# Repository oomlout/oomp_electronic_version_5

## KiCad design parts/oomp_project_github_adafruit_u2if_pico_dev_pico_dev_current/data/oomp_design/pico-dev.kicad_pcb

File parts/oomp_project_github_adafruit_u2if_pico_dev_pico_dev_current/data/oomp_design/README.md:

# OOMP KiCad design copy

Open `pico-dev.kicad_pro` (or the `.kicad_pcb` / `.kicad_sch`) in KiCad. Local OOMP libraries are under `libraries/`. Original inputs are preserved in [../original/](../original/).

Only verified unchanged installed KiCad defaults were renamed. Modified, custom, unmatched and unavailable items remain unchanged. Soldering variants are never swapped during conversion. Existing pad coordinates, nets and UUIDs are preserved.

See [conversion_report.yaml](conversion_report.yaml) for every conversion and skip. Copy this directory before editing; regeneration refuses to overwrite edited design files.

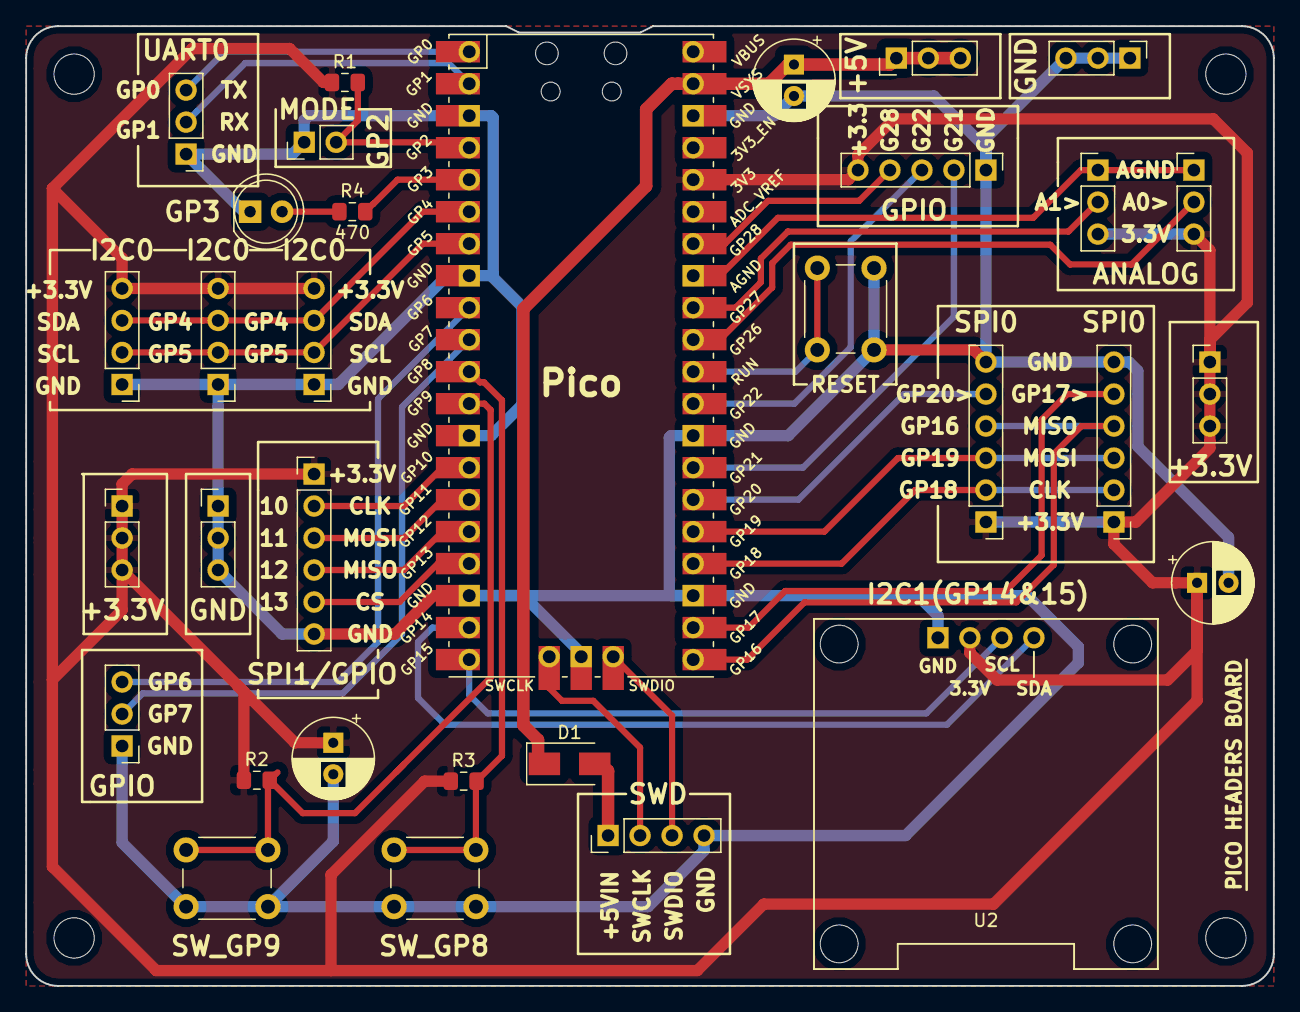
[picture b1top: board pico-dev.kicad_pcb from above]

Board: 2 copper layers, 99.1 x 76.2 mm, 36 parts (0 on the bottom side), 35 nets.

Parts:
C1, C2, C3: CP; CP_Radial_D6.3mm_P2.50mm
D1: SS14; D_SMA
D2: LED; LED_D5.0mm
H1, H2, H3, H4: MountingHole; MountingHole_3.2mm_M3
J1: MODE; PinHeader_1x02_P2.54mm_Vertical
J2: SWD; PinHeader_1x04_P2.54mm_Vertical
J3: AN0_GP26; PinHeader_1x03_P2.54mm_Vertical
J4: AN1_GP27; PinHeader_1x03_P2.54mm_Vertical
J5, J6, J7: I2C0; PinHeader_1x04_P2.54mm_Vertical
J8: UART0; PinHeader_1x03_P2.54mm_Vertical
J9, J10: SPI0; PinHeader_1x06_P2.54mm_Vertical
J11: GPIO; PinHeader_1x05_P2.54mm_Vertical
J12: SPI1/GPIO; PinHeader_1x06_P2.54mm_Vertical
J13, J17: +3.3V; PinHeader_1x03_P2.54mm_Vertical
J14: +5V; PinHeader_1x03_P2.54mm_Vertical
J15, J16: GND; PinHeader_1x03_P2.54mm_Vertical
J18: GPIO; PinHeader_1x03_P2.54mm_Vertical
R1, R2, R3: 10k; R_0805_2012Metric_Pad1.15x1.40mm_HandSolder
R4: 470; R_0805_2012Metric_Pad1.15x1.40mm_HandSolder
SW1: SW_RST; SW_PUSH_6mm_H4.3mm
SW2: SW_GP9; SW_PUSH_6mm_H4.3mm
SW3: SW_GP8; SW_PUSH_6mm_H4.3mm
U1: Pico; RPi_Pico_SMD_TH
U2: SSD1306_I2C; ssd1306_I2c

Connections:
+3V3: C2.1, C3.1, J3.3, J4.3, J5.4, J6.4, J7.4, J9.1, J10.1, J11.5, J12.1, J13.1, J13.2, J13.3, J17.1, J17.2, J17.3, R1.1, R2.1, R3.1, U1.36, U2.2
+5V: C1.1, D1.1, J14.1, J14.2, J14.3, U1.39
+5VD: D1.2, J2.1
ADC0: J3.2, U1.31
ADC1: J4.2, U1.32
AGND: J3.1, J4.1, U1.33
GND: C1.2, C2.2, C3.2, D2.1, J1.1, J2.4, J5.1, J6.1, J7.1, J8.1, J9.6, J10.6, J11.1, J12.6, J15.1, J15.2, J15.3, J16.1, J16.2, J16.3, J18.1, SW1.2, SW2.2, SW3.2, U1.3, U1.8, U1.13, U1.18, U1.23, U1.28, U1.38, U1.42, U2.1
GP6: J18.3, U1.9
GP7: J18.2, U1.10
GP8: R3.2, SW3.1, U1.11
GP9: R2.2, SW2.1, U1.12
GP21: J11.2, U1.27
GP22: J11.3, U1.29
GP28: J11.4, U1.34
LED0: R4.2, U1.5
MODE: J1.2, R1.2, U1.4
unnamed: D2.2, R4.1
RUN: SW1.1, U1.30
SCL_0: J5.2, J6.2, J7.2, U1.7
SCL_1: U1.20, U2.3
SDA_0: J5.3, J6.3, J7.3, U1.6
SDA_1: U1.19, U2.4
SPI0_CK: J9.2, J10.2, U1.24
SPI0_CS1: J9.5, U1.22
SPI0_CS2: J10.5, U1.26
SPI0_MISO: J9.4, J10.4, U1.21
SPI0_MOSI: J9.3, J10.3, U1.25
SPI1_CK_GP10: J12.2, U1.14
SPI1_CS1_GP13: J12.5, U1.17
SPI1_MISO_GP12: J12.4, U1.16
SPI1_MOSI_GP11: J12.3, U1.15
SWCLK: J2.2, U1.41
SWDIO: J2.3, U1.43
U_RX: J8.2, U1.2
U_TX: J8.3, U1.1

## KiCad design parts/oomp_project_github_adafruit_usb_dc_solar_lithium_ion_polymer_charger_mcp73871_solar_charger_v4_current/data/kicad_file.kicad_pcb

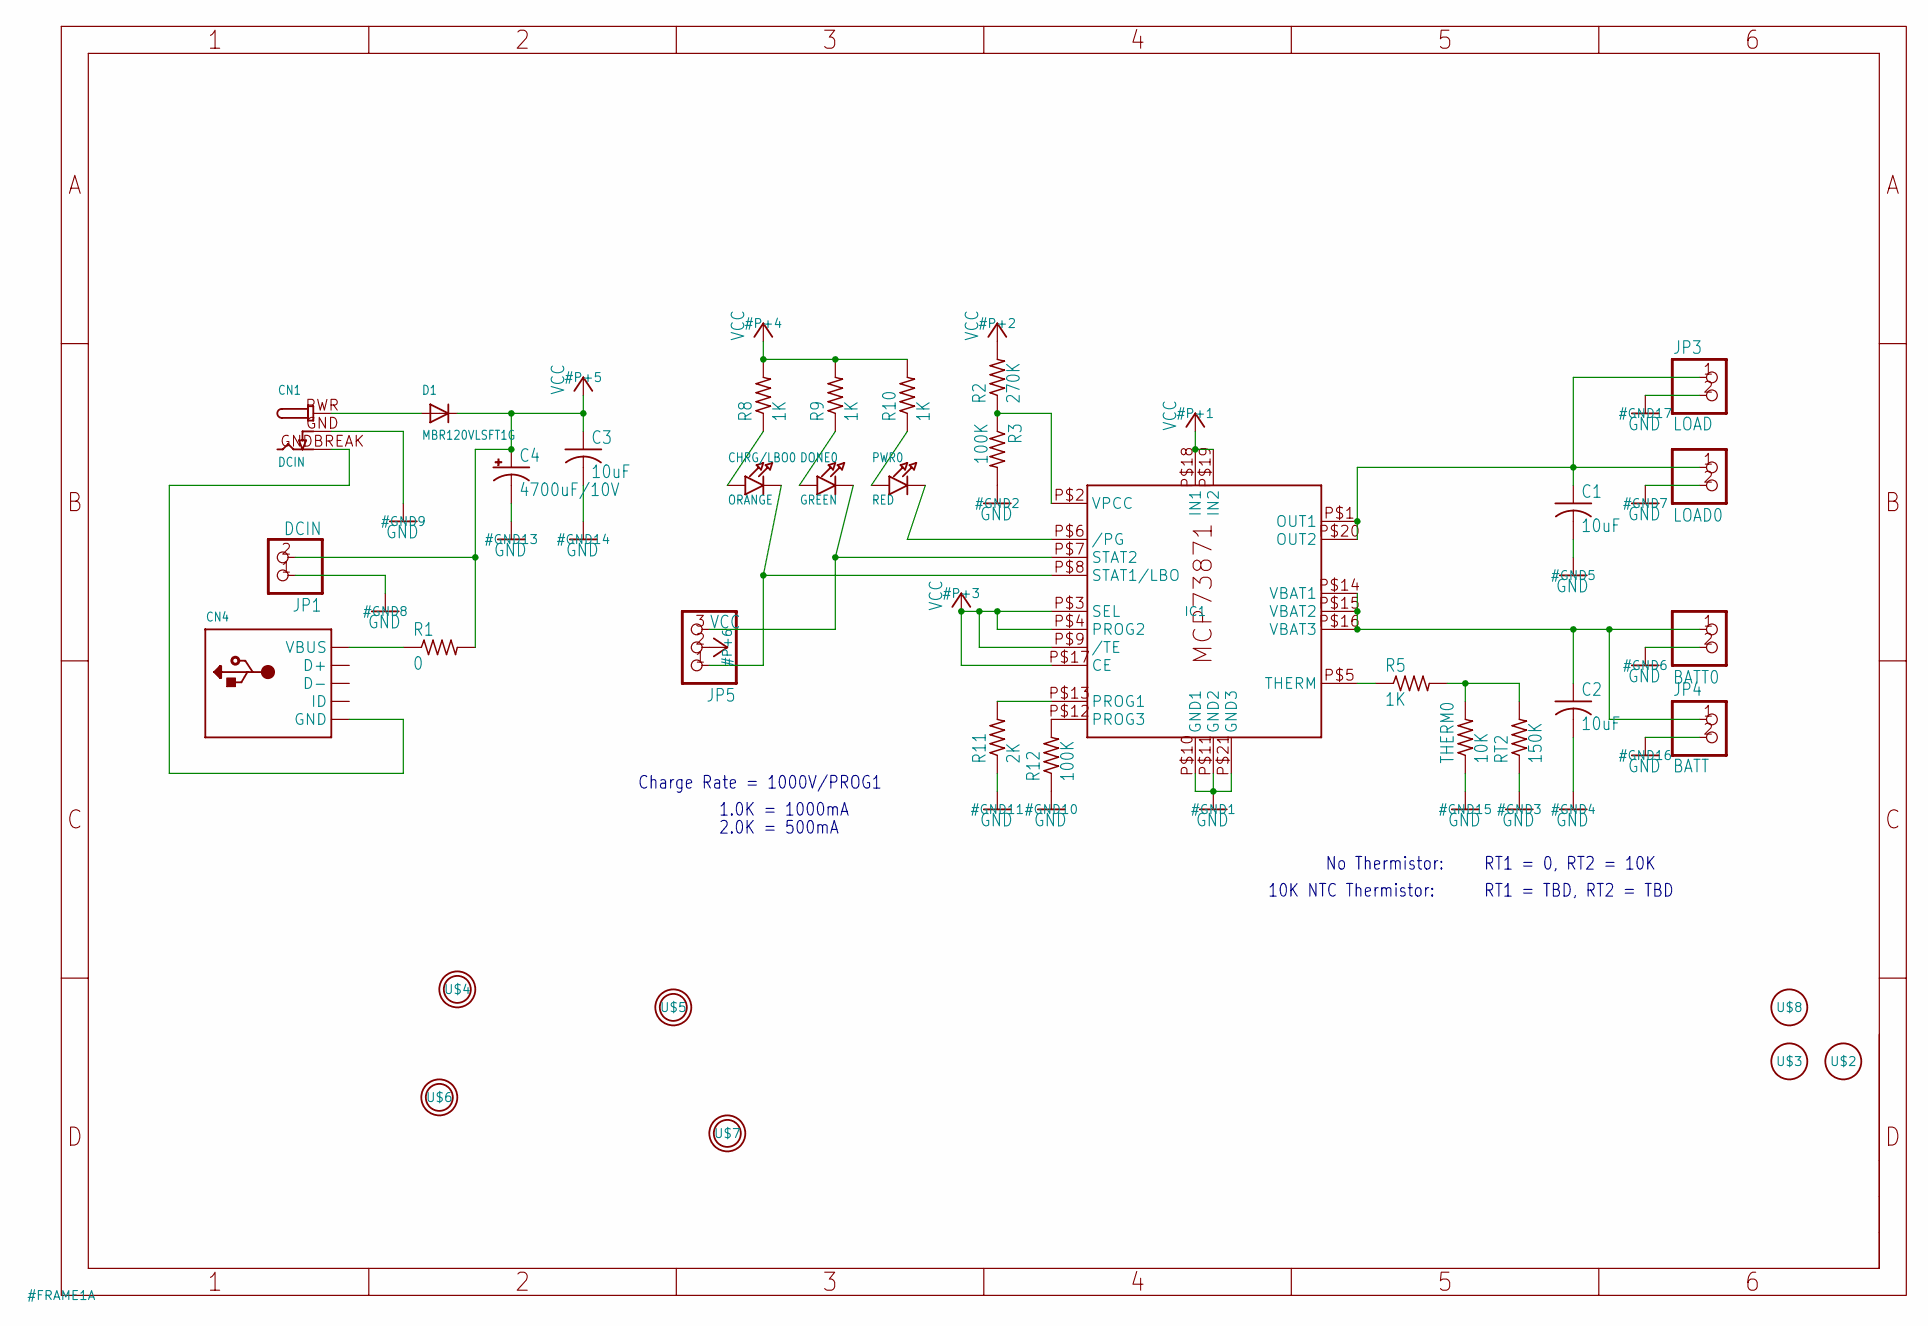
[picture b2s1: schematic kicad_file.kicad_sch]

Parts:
BATT0: JST_2PIN-SMT-RA; JST-PH-2-SMT-RA
C1, C2, C3: 10uF; C0805K
C4: 4700uF/10V; E5-13
CHRG/LBO0: ORANGE; CHIPLED_0805_NOOUTLINE
CN1: DCIN; DCJACK_2MM_SMT
CN4: USBMINIBLARGE; USB-MINIB_LARGER
D1: MBR120VLSFT1G; SOD-123
DONE0: GREEN; CHIPLED_0805_NOOUTLINE
IC1: MCP73871; QFN20_4MM
JP1: DCIN; 1X02_OVAL
JP3: LOAD; 1X02_ROUND
JP4: BATT; 1X02_ROUND
JP5: PINHD-1X3CB; 1X03-CLEANBIG
LOAD0: JST_2PIN-SMT-RA; JST-PH-2-SMT-RA
PWR0: RED; CHIPLED_0805_NOOUTLINE
R1: 0; R0805
R2: 270K; R0805
R3, R12: 100K; R0805
R5: 1K; M0805
R8, R9, R10: 1K; R0805
R11: 2K; 0805-THM
RT2: 150K; M0805
THERM0: 10K; 0805-THM
U$2, U$3, U$8: FIDUCIAL; FIDUCIAL_1MM
U$4, U$5, U$6, U$7: MOUNTINGHOLE2.5; MOUNTINGHOLE_2.5_PLATED

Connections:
BATT: BATT0.1 (2), C2.1, IC1.P$14 (VBAT1), IC1.P$15 (VBAT2), IC1.P$16 (VBAT3), JP4.1
GND: BATT0.2 (1), C1.2, C2.2, C3.2, C4.-, CN1.GND (GNDBREAK), IC1.P$10 (GND1), IC1.P$11 (GND2), IC1.P$21 (GND3), JP1.1, JP3.2, JP4.2, LOAD0.2 (1), R3.2, R11.1, R12.1, RT2.1, THERM0.1
unnamed: IC1.P$6 (/PG), PWR0.C
unnamed: CN4.VBUS, R1.1
unnamed: CN1.GNDBREAK (GND), CN4.GND, CN4.GND1 (GND), CN4.GND2 (GND), CN4.GND3 (GND), CN4.GND4 (GND)
unnamed: DONE0.C, IC1.P$7 (STAT2), JP5.3
unnamed: IC1.P$5 (THERM), R5.1
unnamed: IC1.P$2 (VPCC), R2.1, R3.1
unnamed: R5.2, RT2.2, THERM0.2
unnamed: CN1.PWR, D1.A
unnamed: CHRG/LBO0.C, IC1.P$8 (STAT1/LBO), JP5.1
unnamed: CHRG/LBO0.A, R8.1
unnamed: DONE0.A, R9.1
unnamed: PWR0.A, R10.1
unnamed: IC1.P$12 (PROG3), R12.2
unnamed: IC1.P$13 (PROG1), R11.2
OUT: C1.1, IC1.P$1 (OUT1), IC1.P$20 (OUT2), JP3.1, LOAD0.1 (2)
VCC: C3.1, C4.+, D1.C, IC1.P$3 (SEL), IC1.P$4 (PROG2), IC1.P$9 (/TE), IC1.P$17 (CE), IC1.P$18 (IN1), IC1.P$19 (IN2), JP1.2, JP5.2, R1.2, R2.2, R8.2, R9.2, R10.2

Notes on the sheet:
1.0K = 1000mA
RT1 = 0, RT2 = 10K
Charge Rate = 1000V/PROG1
2.0K = 500mA
No Thermistor:
10K NTC Thermistor:
RT1 = TBD, RT2 = TBD

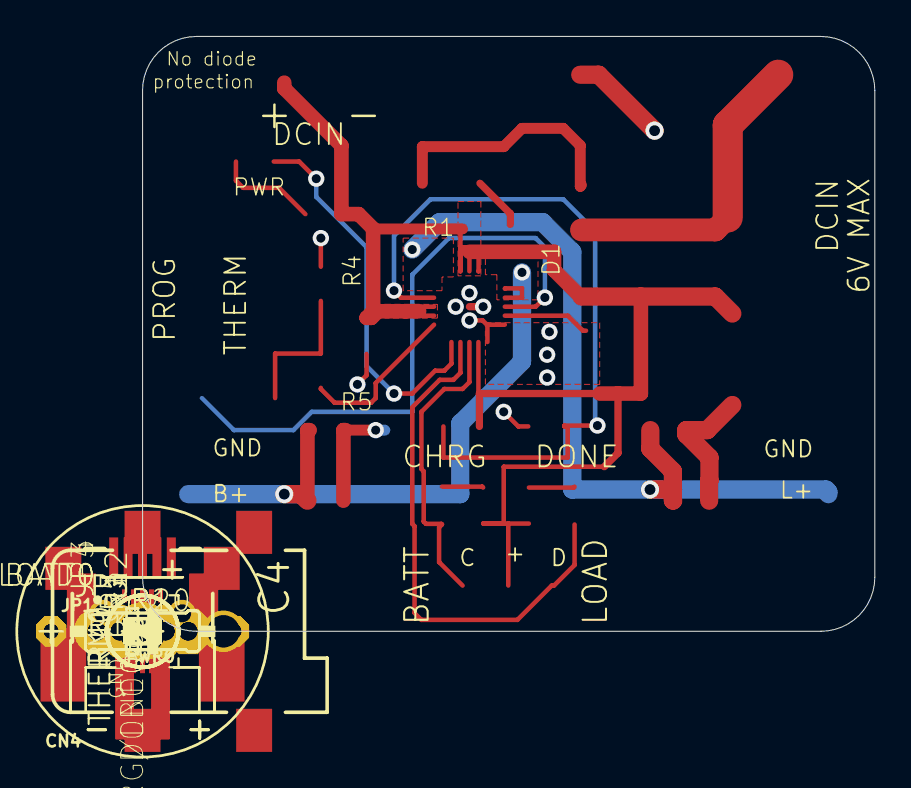
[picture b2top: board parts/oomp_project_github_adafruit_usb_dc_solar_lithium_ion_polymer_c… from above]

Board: 16 copper layers, 40.7 x 33.0 mm, 36 parts (1 on the bottom side), 18 nets.

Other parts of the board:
U$1: ADAFRUIT_TEXT_20MM

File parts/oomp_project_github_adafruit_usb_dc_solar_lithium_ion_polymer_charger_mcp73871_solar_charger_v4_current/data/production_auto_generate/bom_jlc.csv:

Comment,Designator,Footprint,LCSC Part #
,JP5,Adafruit MCP73871 Solar Charger v4-import-fps:1X03-CLEANBIG,C49257
,U$1,Adafruit MCP73871 Solar Charger v4-import-fps:ADAFRUIT_TEXT_20MM,
,"BATT0,LOAD0",Adafruit MCP73871 Solar Charger v4-import-fps:JST-PH-2-SMT-RA,
,CN4,Adafruit MCP73871 Solar Charger v4-import-fps:USB-MINIB_LARGER,
0,R1,Adafruit MCP73871 Solar Charger v4-import-fps:R0805,C2907288
100K,"R3,R12",Adafruit MCP73871 Solar Charger v4-import-fps:R0805,C149504
10K,THERM0,Adafruit MCP73871 Solar Charger v4-import-fps:0805-THM,
10uF,"C1,C2,C3",Adafruit MCP73871 Solar Charger v4-import-fps:C0805K,
150K,RT2,Adafruit MCP73871 Solar Charger v4-import-fps:M0805,C2907228
1K,R5,Adafruit MCP73871 Solar Charger v4-import-fps:M0805,C17513
1K,"R8,R9,R10",Adafruit MCP73871 Solar Charger v4-import-fps:R0805,C17513
270K,R2,Adafruit MCP73871 Solar Charger v4-import-fps:R0805,C2930189
2K,R11,Adafruit MCP73871 Solar Charger v4-import-fps:0805-THM,C17604
4700uF/10V,C4,Adafruit MCP73871 Solar Charger v4-import-fps:E5-13,
BATT,JP4,Adafruit MCP73871 Solar Charger v4-import-fps:1X02_ROUND,C492401
DCIN,JP1,Adafruit MCP73871 Solar Charger v4-import-fps:1X02_OVAL,C492401
DCIN,CN1,Adafruit MCP73871 Solar Charger v4-import-fps:DCJACK_2MM_SMT,
FIDUCIAL,"U$2,U$3,U$8",Adafruit MCP73871 Solar Charger v4-import-fps:FIDUCIAL_1MM,
GREEN,DONE0,Adafruit MCP73871 Solar Charger v4-import-fps:CHIPLED_0805_NOOUTLINE,
LOAD,JP3,Adafruit MCP73871 Solar Charger v4-import-fps:1X02_ROUND,C492401
MBR120VLSFT1G,D1,Adafruit MCP73871 Solar Charger v4-import-fps:SOD-123,
MCP73871,IC1,Adafruit MCP73871 Solar Charger v4-import-fps:QFN20_4MM,
ORANGE,CHRG/LBO0,Adafruit MCP73871 Solar Charger v4-import-fps:CHIPLED_0805_NOOUTLINE,
RED,PWR0,Adafruit MCP73871 Solar Charger v4-import-fps:CHIPLED_0805_NOOUTLINE,

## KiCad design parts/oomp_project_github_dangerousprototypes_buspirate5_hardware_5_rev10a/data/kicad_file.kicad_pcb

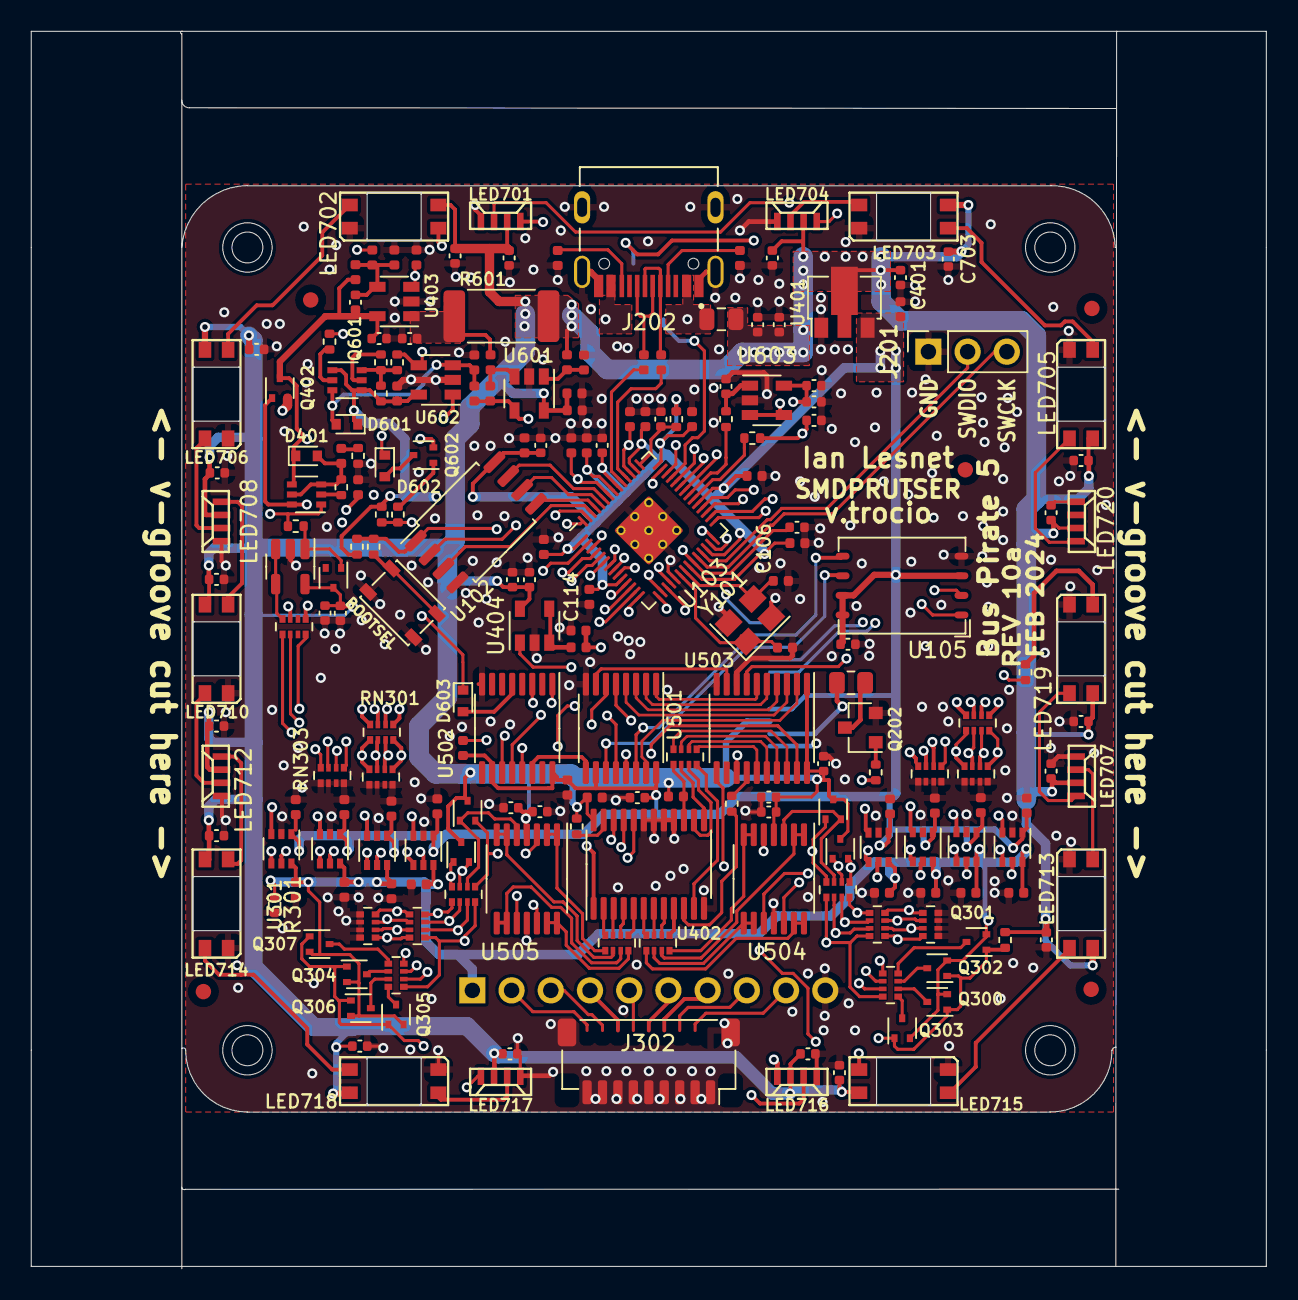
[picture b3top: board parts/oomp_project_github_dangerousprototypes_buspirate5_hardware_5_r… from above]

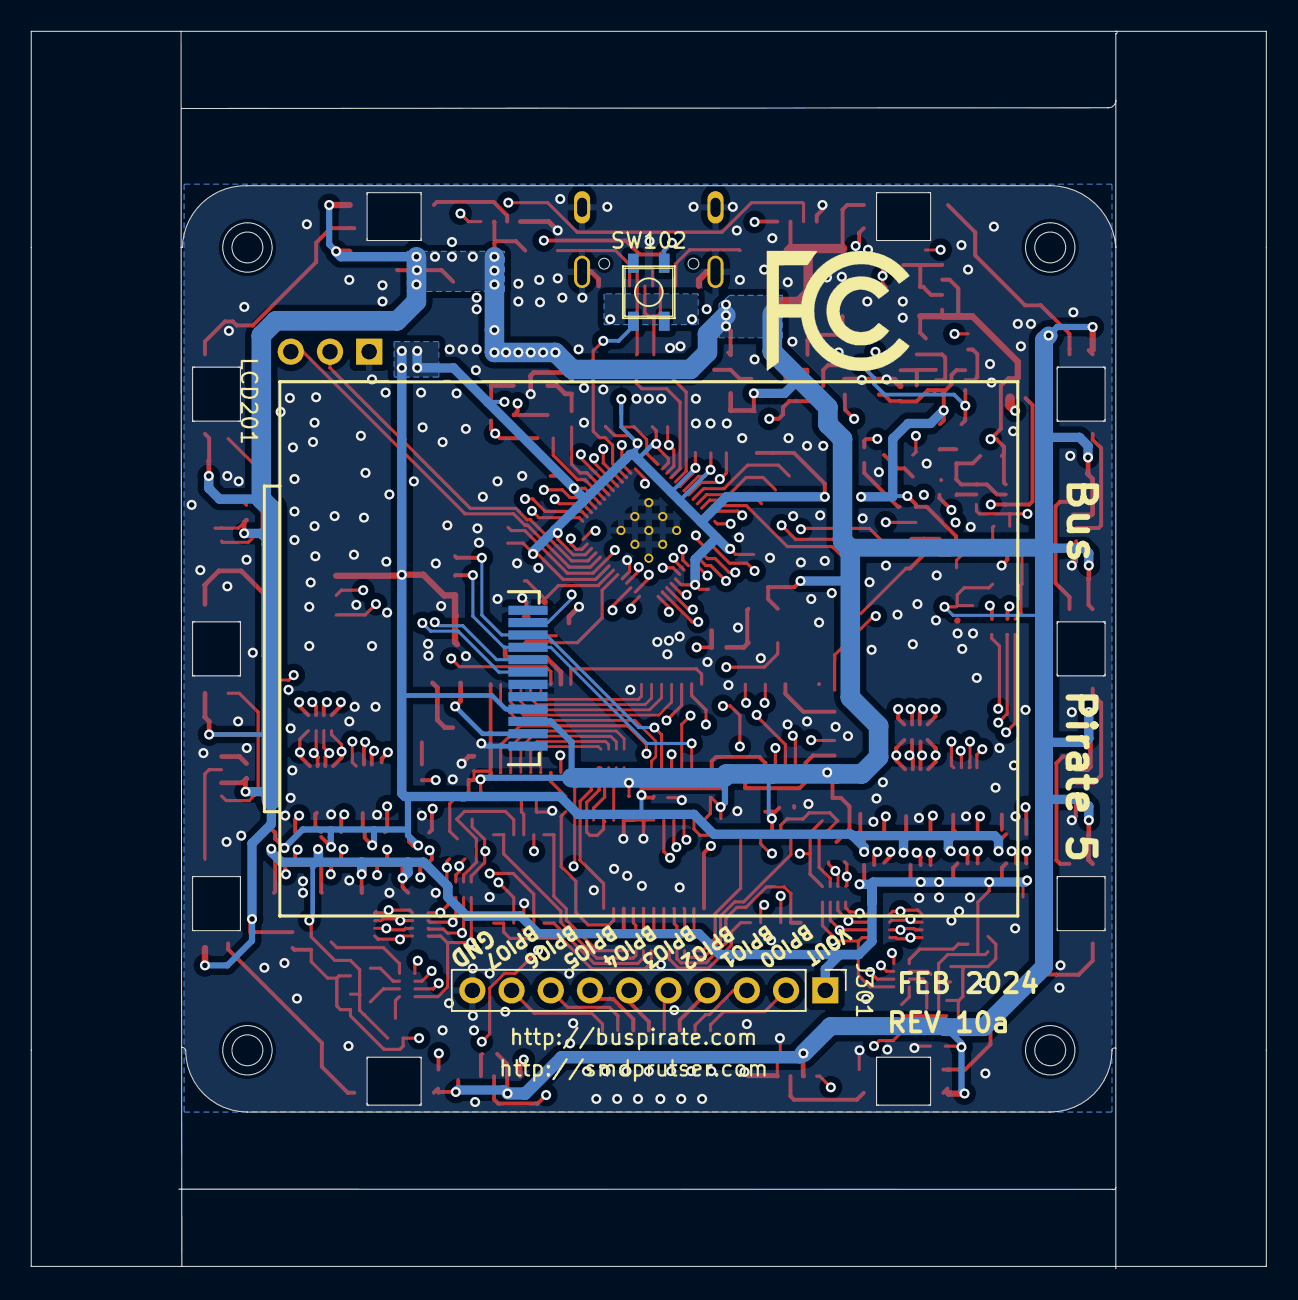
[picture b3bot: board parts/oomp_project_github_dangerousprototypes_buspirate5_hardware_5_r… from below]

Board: 4 copper layers, 80.0 x 80.0 mm, 220 parts (4 on the bottom side), 183 nets.

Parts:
C103, C110, C111, C112, C113, C114, C115, C116, C117, C118, C121, C301, C302, C303, C304, C305, C306, C307, C308, C309, C310, C311, C312, C313, C314, C315, C316, C403, C406, C414, C415, C416, C501, C502, C503, C506, C508, C510, C602, C605, C701, C702, C703, C704, C705, C706, C707, C708, C710, C712, C713, C714, C715, C716, C717, C718, C719, C720: 0.1uF; C_0402_1005Metric
C104, C107, C108, C109, C405, C413, C504, C507, C509, C601: 2.2uF; C_0402_1005Metric
C105, C106: 15pF; C_0402_1005Metric
C201, C202, C401, C402, C404, C407: 4.7uF; C_0402_1005Metric
C408: 120pF; C_0402_1005Metric
C603: DNF; C_0402_1005Metric
D401, D601, D602, D603: 1N4148WT; D_SOD-523
D500, D501, D502, D503, D504: BAS40T-05; SOT-523
FID1, FID2, FID3, FID4, FID5: Fiducial; Fiducial_1mm_Mask2mm
H1, H2, H3, H4: MountingHole; MountingHole_3.2mm_M3
J201: Conn_01x03; PinSocket_1x03_P2.54mm_Vertical
J202: TYPE-C-31-M-12; HRO_TYPE-C-31-M-12
J301: Conn_01x10; PinHeader_1x10_P2.54mm_Vertical
J302: Conn_01x09; JST_SH_SM09B-SRSS-TB_1x09-1MP_P1.00mm_Horizontal
L201: 1.5A; L_0805_2012Metric
LCD201: TFT_20_QT200H1201
LED701, LED704, LED707, LED708, LED712, LED716, LED717, LED720: SK6812-side-a_b
LED702, LED703, LED705, LED706, LED710, LED713, LED714, LED715, LED718, LED719: SK6812-mini-e
Q202: MMBT7002K; SOT-23
Q300, Q301, Q302, Q303, Q304, Q305, Q306, Q307, Q402, Q602: SI2301; SOT-523
Q401: BCM857; SOT-363_SC-70-6
Q601: MMDT3906; SOT-363_SC-70-6
R101, R502, R602, R603: 1K; R_0402_1005Metric
R102: DNF; R_0402_1005Metric
R103, R208, R608, R612: 200R; R_0402_1005Metric
R201, R204: 5.1K; R_0402_1005Metric
R202, R203: 22R; R_0402_1005Metric
R209: 33R; R_0805_2012Metric
R301, R313, R402, R406, R407, R410, R414, R415, R501, R606, R609, R610, R611, R613: 10K; R_0402_1005Metric
R316, R320: 510R; R_0402_1005Metric
R319, R401, R412: 100K; R_0402_1005Metric
R403: 102K; R_0402_1005Metric
R404: 133K; R_0402_1005Metric
R405, R408, R409, R604, R605: 33K; R_0402_1005Metric
R601: 0R2; R_2512_6332Metric_Pad1.40x3.35mm_HandSolder
RN301, RN305, RN306, RN309: 330R; R_Array_Convex_4x0402
RN302, RN304, RN307, RN310: 1M; R_Array_Convex_4x0402
RN303, RN308, RN317, RN318: 100K; R_Array_Convex_4x0402
RN311, RN312: 10K; R_Array_Convex_4x0402
RN315, RN400, RN401, RN402: 510R; R_Array_Convex_4x0402
SW101: SW_SPST; SW_SPST_PTS810
SW102: 4P_button_sw; GT-TC026X-HXXX-LX
U102: W25Q128JVSIQ; SOP-8_5.28x5.23mm_P1.27mm
U103: RP2040; RP2040-QFN-56
U105: MT29F1G01ABAFDWB; U-PDFN-8
U301, U302, U303, U304, U305, U306, U307, U308: AiP74LVC1T45GC363.TR; SOT-363_SC-70-6
U401: ME6211A33PG-N; SOT-89-3
U402: CD4067; TSSOP-24_4.4x7.8mm_P0.65mm
U403: AP2127; SOT-23-5
U404, U506, U603: LMV321; SOT-23-5
U501, U502: AIP74HC595TA; TSSOP-16_4.4x5mm_P0.65mm
U503: AIP74HCT245TA; TSSOP-20_4.4x6.5mm_P0.65mm
U504, U505: LMV324; TSSOP-14_4.4x5mm_P0.65mm
U601: LMV321A; SOT-23-5
U602: LMV331; SOT-23-5
Y101: 12Mhz; Crystal_SMD_3225-4Pin_3.2x2.5mm
logo1: fcc_logo; logo_fcc

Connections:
+1V1: C107.1, C117.1, C118.1, U103.23 (DVDD), U103.45 (VREG_VOUT), U103.50 (DVDD)
+3V3: C103.1, C104.1, C108.2, C110.1, C111.1, C112.1, C113.1, C114.1, C115.1, C116.1, C121.1, C301.2, C302.2, C303.2, C307.2, C308.2, C309.2, C313.2, C314.2, C402.1, C413.1, C414.2, C501.2, C502.2, C605.1, D601.1 (K), LCD201.4 (VCC), Q601.1 (E1), Q601.4 (E2), R102.1, R103.1, R501.1, R609.1, R613.1, SW102.4, U102.8 (VCC), U103.1 (IOVDD), U103.10 (IOVDD), U103.22 (IOVDD), U103.26 (RUN), U103.33 (IOVDD), U103.42 (IOVDD), U103.44 (VREG_IN), U103.48 (USB_VDD), U103.49 (IOVDD), U105.3 (WP/IO2), U105.7 (HOLD/IO3), U105.8 (VCC), U301.1 (VCCA), U302.1 (VCCA), U303.1 (VCCA), U304.1 (VCCA), U305.1 (VCCA), U306.1 (VCCA), U307.1 (VCCA), U308.1 (VCCA), U401.3 (VOUT), U501.10 (~SRCLR), U501.16 (VCC), U502.10 (~SRCLR), U502.16 (VCC), U602.5 (V+), U603.5 (V+)
+VUSB: C201.2, C202.2, C401.1, C403.2, C405.2, C406.1, C503.2, C504.2, C506.1, C507.2, C508.2, C509.2, C510.2, C601.1, C602.2, C701.2, C702.2, C703.2, C704.2, C705.2, C706.2, C707.2, C708.2, C710.2, C712.2, C713.2, C714.2, C715.2, C716.2, C717.2, C718.2, C719.2, C720.2, D500.3, D501.3, D502.3, D503.3, D504.3, L201.1, LCD201.3 (LED-A), LED701.3 (VDD), LED702.1 (VDD), LED703.1 (VDD), LED704.3 (VDD), LED705.1 (VDD), LED706.1 (VDD), LED707.3 (VDD), LED708.3 (VDD), LED710.1 (VDD), LED712.3 (VDD), LED713.1 (VDD), LED714.1 (VDD), LED715.1 (VDD), LED716.3 (VDD), LED717.3 (VDD), LED718.1 (VDD), LED719.1 (VDD), LED720.3 (VDD), R313.2, R320.2, R402.1, R601.1, R602.2, U401.2 (VIN), U402.24 (VCC), U404.5 (V+), U503.1 (A->B), U503.20 (VCC), U504.4 (V+), U505.4 (V+), U506.5 (V+), U601.5 (V+)
AMUX_EN: R402.2, RN315.1 (R1.1), U402.15 (~E)
AMUX_OUT: R406.2, R407.2, U103.40 (GPIO28_ADC2)
AMUX_S0: R316.1, U402.10 (S0)
AMUX_S1: RN315.4 (R1.1), U402.11 (S1)
AMUX_S2: RN315.3 (R1.1), U402.14 (S2)
AMUX_S3: RN315.2 (R1.1), U402.13 (S3)
BPIO0: J301.2, J302.1, RN305.1 (R1.1), RN312.1 (R1.1), RN318.8 (R1.8)
BPIO1: J301.3, J302.2, RN305.2 (R1.1), RN312.2 (R1.1), RN318.7 (R1.8)
BPIO2: J301.4, J302.3, RN305.3 (R1.1), RN312.3 (R1.1), RN318.6 (R1.8)
BPIO3: J301.5, J302.4, RN305.4 (R1.1), RN312.4 (R1.1), RN318.5 (R1.8)
BPIO4: J301.6, J302.5, RN309.1 (R1.1), RN311.1 (R1.1), RN317.8 (R1.8)
BPIO5: J301.7, J302.6, RN309.2 (R1.1), RN311.2 (R1.1), RN317.7 (R1.8)
BPIO6: J301.8, J302.7, RN309.3 (R1.1), RN311.3 (R1.1), RN317.6 (R1.8)
BPIO7: J301.9, J302.8, RN309.4 (R1.1), RN311.4 (R1.1), RN317.5 (R1.8)
BUFDIR0: RN303.8 (R1.8), U103.2 (GPIO0), U301.5 (DIR)
BUFDIR1: RN303.7 (R1.8), U103.3 (GPIO1), U302.5 (DIR)
BUFDIR2: RN303.6 (R1.8), U103.4 (GPIO2), U303.5 (DIR)
BUFDIR3: RN303.5 (R1.8), U103.5 (GPIO3), U304.5 (DIR)
BUFDIR4: RN308.8 (R1.8), U103.6 (GPIO4), U305.5 (DIR)
BUFDIR5: RN308.7 (R1.8), U103.7 (GPIO5), U306.5 (DIR)
BUFDIR6: RN308.6 (R1.8), U103.8 (GPIO6), U307.5 (DIR)
BUFDIR7: RN308.5 (R1.8), U103.9 (GPIO7), U308.5 (DIR)
BUFIO0: RN301.8 (R1.8), U103.11 (GPIO8)
BUFIO1: RN301.7 (R1.8), U103.12 (GPIO9)
BUFIO2: RN301.6 (R1.8), U103.13 (GPIO10)
BUFIO3: RN301.5 (R1.8), U103.14 (GPIO11)
BUFIO4: RN306.8 (R1.8), U103.15 (GPIO12)
BUFIO5: RN306.7 (R1.8), U103.16 (GPIO13)
BUFIO6: RN306.6 (R1.8), U103.17 (GPIO14)
BUFIO7: RN306.5 (R1.8), U103.18 (GPIO15)
BUTTONS: SW102.1, U103.39 (GPIO27_ADC1)
CURRENT_ADJ_MCU: R415.2, U103.34 (GPIO22)
CURRENT_DETECT: Q602.2 (S), R610.2, RN402.5 (R1.8), U602.4
CURRENT_EN: R612.2, R613.2, U502.1 (QB)
CURRENT_EN_OVERRIDE: D603.2 (A), U502.5 (QF)
CURRENT_RESET: R611.1, U502.3 (QD)
CURRENT_SENSE: R605.1, R606.2, U103.41 (GPIO29_ADC3), U601.4
DISPLAY_BACKLIGHT: R208.1, U501.5 (QF)
DISPLAY_CS: LCD201.8 (CS), U103.37 (GPIO25)
DISPLAY_DP: LCD201.7 (WR/SPI_A0), U103.36 (GPIO24)
DISPLAY_LED-K: LCD201.2 (LED-K), R209.2
DISPLAY_RESET: LCD201.11 (RESET), U501.6 (QG)
GND: C103.2, C104.2, C105.2, C106.2, C107.2, C108.1, C109.2, C110.2, C111.2, C112.2, C113.2, C114.2, C115.2, C116.2, C117.2, C118.2, C121.2, C201.1, C202.1, C301.1, C302.1, C303.1, C304.2, C305.2, C306.2, C307.1, C308.1, C309.1, C310.2, C311.2, C312.2, C313.1, C314.1, C315.2, C316.2, C401.2, C402.2, C403.1, C404.2, C405.1, C406.2, C407.2, C413.2, C414.1, C415.1, C416.1, C501.1, C502.1, C503.1, C504.1, C506.2, C507.1, C508.1, C509.1, C510.1, C601.2, C602.1, C603.1, C605.2, C701.1, C702.1, C703.1, C704.1, C705.1, C706.1, C707.1, C708.1, C710.1, C712.1, C713.1, C714.1, C715.1, C716.1, C717.1, C718.1, C719.1, C720.1, J201.1, J202.A1B12 (GND), J202.B1A12 (GND), J202.S1 (SHIELD), J202.S2 (SHIELD), J202.S3 (SHIELD), J202.S4 (SHIELD), J301.10, J302.9, LCD201.1 (GND), LCD201.5 (GND), LCD201.6 (GND), LCD201.12 (GND), LED701.1 (VSS), LED702.3 (VSS), LED703.3 (VSS), LED704.1 (VSS), LED705.3 (VSS), LED706.3 (VSS), LED707.1 (VSS), LED708.1 (VSS), LED710.3 (VSS), LED712.1 (VSS), LED713.3 (VSS), LED714.3 (VSS), LED715.3 (VSS), LED716.1 (VSS), LED717.1 (VSS), LED718.3 (VSS), LED719.3 (VSS), LED720.1 (VSS), Q202.2 (S), R201.1, R204.1, R301.2, R401.2, R405.2, R407.1, R409.2, R412.2, R604.1, RN302.1 (R1.1), RN302.2 (R1.1), RN302.3 (R1.1), RN302.4 (R1.1), RN303.1 (R1.1), RN303.2 (R1.1), RN303.3 (R1.1), RN303.4 (R1.1), RN304.5 (R1.8), RN304.6 (R1.8), RN304.7 (R1.8), RN304.8 (R1.8), RN307.1 (R1.1), RN307.2 (R1.1), RN307.3 (R1.1), RN307.4 (R1.1), RN308.1 (R1.1), RN308.2 (R1.1), RN308.3 (R1.1), RN308.4 (R1.1), RN310.5 (R1.8), RN310.6 (R1.8), RN310.7 (R1.8), RN310.8 (R1.8), SW101.2 (B), U102.4 (VSS), U103.19 (TESTEN), U103.57 (GND), U105.4 (VSS), U301.2 (GND), U302.2 (GND), U303.2 (GND), U304.2 (GND), U305.2 (GND), U306.2 (GND), U307.2 (GND), U308.2 (GND), U401.1 (GND), U402.12 (GND), U402.16 (I15), U402.17 (I14), U402.18 (I13), U402.19 (I12), U403.2 (GND), U404.2 (V-), U501.8 (GND), U502.8 (GND), U503.8 (A6), U503.10 (GND), U504.11 (V-), U505.11 (V-), U506.2 (V-), U601.2 (V-), U602.2 (V-), U603.2 (V-), Y101.2, Y101.4
LEDS_CDO: R502.1, U503.13 (B5)
MUX_BPIO0: RN401.5 (R1.8), U505.1, U505.2 (-)
MUX_BPIO1: RN401.6 (R1.8), U505.6 (-), U505.7
MUX_BPIO2: RN401.7 (R1.8), U505.8, U505.9 (-)
MUX_BPIO3: RN401.8 (R1.8), U505.13 (-), U505.14
MUX_BPIO4: RN400.5 (R1.8), U504.13 (-), U504.14
MUX_BPIO5: RN400.6 (R1.8), U504.8, U504.9 (-)
MUX_BPIO6: RN400.7 (R1.8), U504.1, U504.2 (-)
MUX_BPIO7: RN400.8 (R1.8), U504.6 (-), U504.7
MUX_VREF_VOUT: RN402.8 (R1.8), U506.3 (-), U506.4
unnamed: D401.2 (A), Q401.3 (C2), Q401.5 (B2), R408.2, R410.2
unnamed: C603.2, D601.2 (A), Q601.3 (C2), R606.1, U602.3 (-)
unnamed: D602.2 (A), Q602.3 (D)
unnamed: J202.A5 (CC1), R201.2
unnamed: J202.B5 (CC2), R204.2
unnamed: J202.A4B9 (VBUS), J202.B4A9 (VBUS), L201.2
unnamed: LED701.4 (DI), LED702.2 (DO)
unnamed: LED701.2 (DO), LED704.4 (DI)
unnamed: LED702.4 (DI), LED706.2 (DO)
unnamed: LED703.4 (DI), LED704.2 (DO)
unnamed: LED703.2 (DO), LED705.4 (DI)
unnamed: LED705.2 (DO), LED720.4 (DI)
unnamed: LED706.4 (DI), LED708.2 (DO)
unnamed: LED707.4 (DI), LED719.2 (DO)
unnamed: LED707.2 (DO), LED713.4 (DI)
unnamed: LED708.4 (DI), LED710.2 (DO)
unnamed: LED710.4 (DI), LED712.2 (DO)
unnamed: LED712.4 (DI), LED714.2 (DO)
unnamed: LED713.2 (DO), LED715.4 (DI)
unnamed: LED714.4 (DI), LED718.2 (DO)
unnamed: LED715.2 (DO), LED716.4 (DI)
unnamed: LED716.2 (DO), LED717.4 (DI)
unnamed: LED717.2 (DO), LED718.4 (DI)
unnamed: LED719.4 (DI), R502.2
unnamed: Q202.3 (D), R209.1
unnamed: Q202.1 (G), R208.2
unnamed: Q300.3 (D), RN311.6 (R1.8)
unnamed: Q301.3 (D), RN311.8 (R1.8)
unnamed: Q302.3 (D), RN311.7 (R1.8)
unnamed: Q303.3 (D), RN311.5 (R1.8)
unnamed: Q304.3 (D), RN312.6 (R1.8)
unnamed: Q305.3 (D), RN312.8 (R1.8)
unnamed: Q306.3 (D), RN312.7 (R1.8)
unnamed: Q307.3 (D), RN312.5 (R1.8)
unnamed: Q401.2 (B1), R410.1
unnamed: Q401.6 (C1), Q402.1 (G), R412.1
unnamed: Q601.2 (B1), R611.2
unnamed: Q601.6 (C1), R608.2, R609.2, R610.1
unnamed: Q601.5 (B2), R608.1
unnamed: Q602.1 (G), R612.1
unnamed: R408.1, R409.1
unnamed: RN301.1 (R1.1), RN302.8 (R1.8), U301.3 (A)
unnamed: RN301.2 (R1.1), RN302.7 (R1.8), U302.3 (A)
unnamed: RN301.3 (R1.1), RN302.6 (R1.8), U303.3 (A)
unnamed: RN301.4 (R1.1), RN302.5 (R1.8), U304.3 (A)
unnamed: RN304.1 (R1.1), RN305.8 (R1.8), U301.4 (B)
unnamed: RN304.2 (R1.1), RN305.7 (R1.8), U302.4 (B)
unnamed: RN304.3 (R1.1), RN305.6 (R1.8), U303.4 (B)
unnamed: RN304.4 (R1.1), RN305.5 (R1.8), U304.4 (B)
unnamed: RN306.1 (R1.1), RN307.8 (R1.8), U305.3 (A)
unnamed: RN306.2 (R1.1), RN307.7 (R1.8), U306.3 (A)
unnamed: RN306.3 (R1.1), RN307.6 (R1.8), U307.3 (A)
unnamed: RN306.4 (R1.1), RN307.5 (R1.8), U308.3 (A)
unnamed: RN309.8 (R1.8), RN310.1 (R1.1), U305.4 (B)
unnamed: RN309.7 (R1.8), RN310.2 (R1.1), U306.4 (B)
unnamed: RN309.6 (R1.8), RN310.3 (R1.1), U307.4 (B)
unnamed: RN309.5 (R1.8), RN310.4 (R1.1), U308.4 (B)
unnamed: RN315.8 (R1.8), U503.18 (B0)
unnamed: RN315.7 (R1.8), U503.17 (B1)
unnamed: RN315.6 (R1.8), U503.16 (B2)
unnamed: RN315.5 (R1.8), U503.15 (B3)
unnamed: D502.2, RN317.1 (R1.1), U504.12 (+)
unnamed: D502.1, RN317.2 (R1.1), U504.10 (+)
unnamed: D501.2, RN317.3 (R1.1), U504.3 (+)
unnamed: D501.1, RN317.4 (R1.1), U504.5 (+)
unnamed: D504.2, RN318.1 (R1.1), U505.3 (+)
unnamed: D504.1, RN318.2 (R1.1), U505.5 (+)
unnamed: D503.2, RN318.3 (R1.1), U505.10 (+)
unnamed: D503.1, RN318.4 (R1.1), U505.12 (+)
unnamed: RN400.1 (R1.1), U402.9 (I0)
unnamed: RN400.2 (R1.1), U402.8 (I1)
unnamed: RN400.3 (R1.1), U402.7 (I2)
unnamed: RN400.4 (R1.1), U402.6 (I3)
unnamed: RN401.1 (R1.1), U402.5 (I4)
unnamed: RN401.2 (R1.1), U402.4 (I5)
unnamed: RN401.3 (R1.1), U402.3 (I6)
unnamed: RN401.4 (R1.1), U402.2 (I7)
unnamed: RN402.1 (R1.1), U402.20 (I11)
unnamed: RN402.2 (R1.1), U402.21 (I10)
unnamed: RN402.4 (R1.1), U402.22 (I9)
unnamed: R101.2, SW101.1 (A)
unnamed: C109.1, R103.2, U103.43 (ADC_AVDD)
unnamed: C105.1, U103.20 (XIN), Y101.1
unnamed: C106.1, U103.21 (XOUT), Y101.3
unnamed: U402.1 (COM), U404.1 (+)
unnamed: R320.1, U402.23 (I8)
unnamed: C408.2, R403.2, R404.2, R405.1, U403.4 (ADJ)
unnamed: R406.1, U404.3 (-), U404.4
unnamed: U501.15 (QA), U503.2 (A0)
unnamed: U501.1 (QB), U503.6 (A4)
unnamed: U501.2 (QC), U503.5 (A3)
unnamed: U501.3 (QD), U503.4 (A2)
unnamed: U501.4 (QE), U503.3 (A1)
unnamed: U501.9 (QH'), U502.14 (SER)
unnamed: U501.7 (QH), U503.9 (A7)
unnamed: R316.2, U503.14 (B4)
unnamed: D500.1, R319.1, U506.1 (+)
unnamed: R602.1, R604.2, U601.1 (+)
unnamed: R603.1, R605.2, U601.3 (-)
unnamed: C416.2, R415.1, U602.1 (+)
unnamed: C415.2, R414.1, U603.1 (+)
PULLUP_EN: Q300.1 (G), Q301.1 (G), Q302.1 (G), Q303.1 (G), Q304.1 (G), Q305.1 (G), Q306.1 (G), Q307.1 (G), R313.1, U503.11 (B7)
QSPI_SCLK: U102.6 (CLK), U103.52 (QSPI_SCLK)
QSPI_SD0: U102.5 (DI), U103.53 (QSPI_SD0)
QSPI_SD1: U102.2 (DO), U103.55 (QSPI_SD1)
QSPI_SD2: U102.3 (WP), U103.54 (QSPI_SD2)
QSPI_SD3: U102.7 (HOLD), U103.51 (QSPI_SD3)
QSPI_SS: R101.1, R102.2, U102.1 (CS), U103.56 (QSPI_SS)
RGB_CDO: U103.28 (GPIO17), U503.7 (A5)
SD_CS: U103.38 (GPIO26_ADC0), U105.1 (CS)
SHIFT_EN: R501.2, U103.32 (GPIO21), U501.13 (~OE), U502.13 (~OE), U503.19 (CE)
SHIFT_LATCH: U103.31 (GPIO20), U501.12 (RCLK), U502.12 (RCLK)
SPI_CDI: U103.27 (GPIO16), U105.2 (SO/IO1)
SPI_CDO: LCD201.10 (SPI_SDA), U103.30 (GPIO19), U105.5 (SI/IO0), U501.14 (SER)
SPI_CLK: LCD201.9 (RS/SPI_SCL), U103.29 (GPIO18), U105.6 (SCK), U501.11 (SRCLK), U502.11 (SRCLK)
SWCLK: J201.3, U103.24 (SWCLK)
SWDIO: J201.2, U103.25 (SWD)
USB_D+: R203.1, U103.47 (USB_DP)
USB_D-: R202.1, U103.46 (USB_DM)
USB_N: J202.A7 (DN1), J202.B7 (DN2), R202.2
USB_P: J202.A6 (DP1), J202.B6 (DP2), R203.2
VREF_VOUT: C304.1, C305.1, C306.1, C310.1, C311.1, C312.1, C315.1, C316.1, J301.1, Q300.2 (S), Q301.2 (S), Q302.2 (S), Q303.2 (S), Q304.2 (S), Q305.2 (S), Q306.2 (S), Q307.2 (S), Q401.1 (E1), Q402.2 (S), R301.1, R319.2, U301.6 (VCCB), U302.6 (VCCB), U303.6 (VCCB), U304.6 (VCCB), U305.6 (VCCB), U306.6 (VCCB), U307.6 (VCCB), U308.6 (VCCB)
VREG_ADJ: R403.1, U603.3 (-), U603.4
VREG_ADJ_MCU: R414.2, U103.35 (GPIO23)
VREG_EN: D602.1 (K), D603.1 (K), R401.1, U403.3 (SHUTDOWN)
VREG_OUT: C407.1, C408.1, D401.1 (K), Q401.4 (E2), Q402.3 (D), R404.1, RN402.7 (R1.8), U403.5 (OUT)
VREG_VIN: C404.1, R601.2, R603.2, U403.1 (VIN)

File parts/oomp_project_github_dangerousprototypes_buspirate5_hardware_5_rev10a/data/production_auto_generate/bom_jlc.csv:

Comment,Designator,Footprint,LCSC Part #
0.1uF,"C103,C110,C111,C112,C113,C114,C115,C116,C117,C118,C121,C301,C302,C303,C304,C305,C306,C307,C308,C309,C310,C311,C312,C313,C314,C315,C316,C403,C406,C414,C415,C416,C501,C502,C503,C506,C508,C510,C602,C605,C701,C702,C703,C704,C705,C706,C707,C708,C710,C712,C713,C714,C715,C716,C717,C718,C719,C720",Capacitor_SMD:C_0402_1005Metric,C60474
0R2,R601,Resistor_SMD:R_2512_6332Metric_Pad1.40x3.35mm_HandSolder,C5119990
1.5A,L201,Inductor_SMD:L_0805_2012Metric,C275464
100K,"R319,R401,R412",Resistor_SMD:R_0402_1005Metric,C25530
100K,"RN303,RN308,RN317,RN318",Resistor_SMD:R_Array_Convex_4x0402,
102K,R403,Resistor_SMD:R_0402_1005Metric,C2933066
10K,"R301,R313,R402,R406,R407,R410,R414,R415,R501,R606,R609,R610,R611,R613",Resistor_SMD:R_0402_1005Metric,C2906861
10K,"RN311,RN312",Resistor_SMD:R_Array_Convex_4x0402,C326872
120pF,C408,Capacitor_SMD:C_0402_1005Metric,C106996
12Mhz,Y101,Crystal:Crystal_SMD_3225-4Pin_3.2x2.5mm,C133334
133K,R404,Resistor_SMD:R_0402_1005Metric,C2998045
15pF,"C105,C106",Capacitor_SMD:C_0402_1005Metric,C106997
1K,"R101,R502,R602,R603",Resistor_SMD:R_0402_1005Metric,C2906864
1M,"RN302,RN304,RN307,RN310",Resistor_SMD:R_Array_Convex_4x0402,
1N4148WT,"D401,D601,D602,D603",Diode_SMD:D_SOD-523,C232841
2.2uF,"C104,C107,C108,C109,C405,C413,C504,C507,C509,C601",Capacitor_SMD:C_0402_1005Metric,C12530
200R,"R103,R208,R608,R612",Resistor_SMD:R_0402_1005Metric,C25087
22R,"R202,R203",Resistor_SMD:R_0402_1005Metric,C114765
330R,"RN301,RN305,RN306,RN309",Resistor_SMD:R_Array_Convex_4x0402,
33K,"R405,R408,R409,R604,R605",Resistor_SMD:R_0402_1005Metric,C2909350
33R,R209,Resistor_SMD:R_0805_2012Metric,C17634
4.7uF,"C201,C202,C401,C402,C404,C407",Capacitor_SMD:C_0402_1005Metric,C368809
4P_button_sw,SW102,dp-switch:GT-TC026X-HXXX-LX,
5.1K,"R201,R204",Resistor_SMD:R_0402_1005Metric,C25905
510R,"R316,R320",Resistor_SMD:R_0402_1005Metric,C276273
510R,"RN315,RN400,RN401,RN402",Resistor_SMD:R_Array_Convex_4x0402,
AIP74HC595TA,"U501,U502",Package_SO:TSSOP-16_4.4x5mm_P0.65mm,C5121351
AIP74HCT245TA,U503,Package_SO:TSSOP-20_4.4x6.5mm_P0.65mm,C5354847
AiP74LVC1T45GC363.TR,"U301,U302,U303,U304,U305,U306,U307,U308",Package_TO_SOT_SMD:SOT-363_SC-70-6,C5162250
AP2127,U403,Package_TO_SOT_SMD:SOT-23-5,C156285
BAS40T-05,"D500,D501,D502,D503,D504",Package_TO_SOT_SMD:SOT-523,C51315104
BCM857,Q401,Package_TO_SOT_SMD:SOT-363_SC-70-6,C105896
CD4067,U402,Package_SO:TSSOP-24_4.4x7.8mm_P0.65mm,C547734
Conn_01x03,J201,Connector_PinSocket_2.54mm:PinSocket_1x03_P2.54mm_Vertical,C2932670
Conn_01x09,J302,Connector_JST:JST_SH_SM09B-SRSS-TB_1x09-1MP_P1.00mm_Horizontal,C160408
Conn_01x10,J301,Connector_PinHeader_2.54mm:PinHeader_1x10_P2.54mm_Vertical,C57369
LMV321,"U404,U506,U603",Package_TO_SOT_SMD:SOT-23-5,C362273
LMV321A,U601,Package_TO_SOT_SMD:SOT-23-5,C431318
LMV324,"U504,U505",Package_SO:TSSOP-14_4.4x5mm_P0.65mm,C398929
LMV331,U602,Package_TO_SOT_SMD:SOT-23-5,C34731
ME6211A33PG-N,U401,Package_TO_SOT_SMD:SOT-89-3,C236673
MMBT7002K,Q202,Package_TO_SOT_SMD:SOT-23,C2879714
MMDT3906,Q601,Package_TO_SOT_SMD:SOT-363_SC-70-6,C2836075
MT29F1G01ABAFDWB,U105,dp-memory:U-PDFN-8,C2905686
RP2040,U103,RP_Silicon:RP2040-QFN-56,C2040
SI2301,"Q300,Q301,Q302,Q303,Q304,Q305,Q306,Q307,Q402,Q602",Package_TO_SOT_SMD:SOT-523,C21714127
SK6812-mini-e,"LED702,LED703,LED705,LED706,LED710,LED713,LED714,LED715,LED718,LED719",dp-LED:SK6812-mini-e,C5149201
SK6812-side-a_b,"LED701,LED704,LED707,LED708,LED712,LED716,LED717,LED720",dp-LED:SK6812-side-a_b,C5378721
SW_SPST,SW101,Button_Switch_SMD:SW_SPST_PTS810,
TFT_20_QT200H1201,LCD201,dp-lcd:TFT_20_QT200H1201,
TYPE-C-31-M-12,J202,usb-c:HRO_TYPE-C-31-M-12,C165948
W25Q128JVSIQ,U102,Package_SO:SOP-8_5.28x5.23mm_P1.27mm,C97521
